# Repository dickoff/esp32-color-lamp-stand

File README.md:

# Color Lamp Stand — User Guide

This illuminated stand connects to Wi-Fi and uses its 32 LEDs to show whether
a stock selected in the firmware is up or down: green for up, red for down, and
white when no current value is available. The stock cannot currently be changed
through the Wi-Fi setup page.

This is the default behavior, but you could modify the software to do something
completely different or custom with the LEDs and the Internet connection.

## Hardware

You need:

- A USB-C wall charger and a USB-C-to-USB-C cable. For full brightness, use a
  charger that provides **5 V at 3 A**.

Good options are:

- This [Anker 20 W USB-C charger kit](https://www.amazon.com/dp/B0CP7NWH6L),
  which includes two compact chargers and two cables. Each charger provides
  5 V at 3 A.
- The inexpensive [IKEA SJÖSS 20 W USB-C charger](https://www.ikea.com/us/en/p/sjoess-20w-1-port-usb-charger-10618445/),
  which also provides 5 V at 3 A. Its USB-C cable is sold separately.

Either option provides enough power for the stand's highest brightness setting.
A computer USB-C port also works, but the stand may automatically use a lower
brightness if the port advertises less available current.

Feed the cable through the base and tie a loose knot inside for strain relief,
as shown below. Do not pull the knot tight enough to damage the cable.

Connect the USB-C plug to the socket on the circuit board.

Fit the translucent cover, then place the object you want to illuminate on top.

## Wi-Fi configuration

On first use, an amber wave travels around the stand and it creates a temporary
Wi-Fi network named
`ColorLamp-Setup-XXXX`, where the last four characters are unique to your stand.

1. On a phone, tablet, or computer, open Wi-Fi settings and join that network.
   It intentionally has no password and may be described by your device as
   having no internet.
2. The setup page should open automatically. If it does not, open
   [http://192.168.4.1](http://192.168.4.1) in a web browser.
3. Select your home Wi-Fi network, enter its password, and choose **Connect**.
4. The stand pulses blue while it tests the connection. Green means setup
   succeeded and the stand will restart. Red means it could not connect; check
   the network and password, then try again.

Your Wi-Fi password is stored only on the stand.

### Changing the Wi-Fi network

With the stand fully started, hold the **BOOT** button on the circuit board for
five seconds. The LEDs turn red, the saved Wi-Fi details are erased, and the
stand restarts in setup mode.

Do not hold **BOOT** while plugging in power or pressing **RESET**. That button
also activates the ESP32's programming mode during startup.

## What the lights during startup mean

Every startup shows the power check, then the firmware version, then the Wi-Fi
status.

### Power check

Immediately after power-on, a short sweep reports how much current the connected
USB-C source advertises. The stand uses this information to limit LED brightness.
The sweep fills, pauses for about a second, and fades away.

- **8 amber LEDs — USB default:** The stand uses a conservative, low-brightness
  limit. For better illumination, try a USB-C charger rated for at least 1.5 A.
- **16 cyan LEDs — 1.5 A:** Normal operation with good available brightness.
- **32 green LEDs — 3 A:** The source advertises the highest supported current.
- **Two red flashes, then 8 amber LEDs:** The stand could not read the source
  capability and safely selected the conservative limit.

This is the capability advertised by the power source, not a measurement of how
much current the stand is presently consuming.

### Firmware version

After the power check, three short displays show the firmware version in
**major.minor.patch** order. Count only the **bright white LEDs** in each display.
The rest of the ring glows dimly in a background color to identify the part:

- **Blue background:** Major version.
- **Purple background:** Minor version.
- **Amber background:** Patch version.

For example, version **2.2.0** shows two white LEDs on blue, two white LEDs on
purple, then an entirely dim amber ring. **No white LEDs means zero**—the colored
background still appears.

### Wi-Fi and setup

After the version display, the entire perimeter shows the Wi-Fi state.

- **Solid blue:** Connecting to the saved Wi-Fi network.
- **Slow amber wave (one lap every four seconds):** Waiting for you to join
  `ColorLamp-Setup-XXXX` and complete setup.
- **Pulsing blue:** Testing the Wi-Fi name and password you entered.
- **Solid green:** Connected successfully. After initial setup, the stand soon
  restarts automatically.
- **Solid red:** The attempted Wi-Fi connection failed.
- **Bright red after holding BOOT:** Saved Wi-Fi details are being erased.

## Troubleshooting

- **The setup page did not open:** Stay connected to `ColorLamp-Setup-XXXX` and
  open [http://192.168.4.1](http://192.168.4.1) manually. Temporarily disabling
  cellular data or a VPN can help if the phone leaves the setup network.
- **The stand keeps returning to amber setup mode:** Re-enter the Wi-Fi password
  and make sure the selected network is available where the stand will be used.
- **The light is unusually dim:** Check the power-on sweep. Eight amber LEDs mean
  the power source advertised only the default USB current; try another USB-C
  charger and cable.
- **You need to start over:** Let the stand finish booting, then hold **BOOT** for
  five seconds.

## Want to modify it?

The hardware and especially firmware are open for experimentation. See the
[modification guide](MODIFYING.md) for the source layout, fixed GPIO assignments,
KiCad design overview, and build workflow.

If you're working with an AI coding agent, point it at this repository and ask
it to read [MODIFYING.md](MODIFYING.md) before making changes.

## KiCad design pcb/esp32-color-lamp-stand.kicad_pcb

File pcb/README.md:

# PCB development

The KiCad project files and the project-local symbol library are the hardware
sources. Edit the schematic in KiCad, update the PCB with `F8`, and route or
refill zones in the PCB Editor.

KiCad 10 and Python 3 are required. On macOS the exporter finds KiCad in
`/Applications/KiCad`; elsewhere, put `kicad-cli` on `PATH` or set
`KICAD_CLI`.

From this directory:

```sh
make check
make manufacturing
```

`make check` runs schematic ERC and PCB DRC, including schematic/PCB parity.
Error-level violations block the command. The latest reports remain available
in `manufacturing/reports/`, including when a check fails. Review warnings in
KiCad before export.

`make manufacturing` performs the checks and writes these upload-ready files
to `manufacturing/jlcpcb/`:

- `esp32-color-lamp-stand-gerbers.zip`
- `jlcpcb_bom.csv`
- `jlcpcb_cpl.csv`
- top and bottom preview images

The exporter omits test points, requires an LCSC number for every assembled
part, and verifies that BOM and CPL designators match. Review the previews and
run JLCPCB's online DFM analysis before ordering.

Some JLCPCB/EasyEDA parts use placement origins or orientations that differ from
the corresponding KiCad footprints. Vendor-specific translation and rotation
corrections for those parts are documented in `jlcpcb-placement-offsets.toml`.
They change only the exported CPL; they do not move PCB footprints or alter the
Gerbers. The exporter looks up each correction by LCSC part number, verifies the
KiCad footprint named in the configuration, rotates local position offsets with
the component, and warns if the expected reference designators have changed.

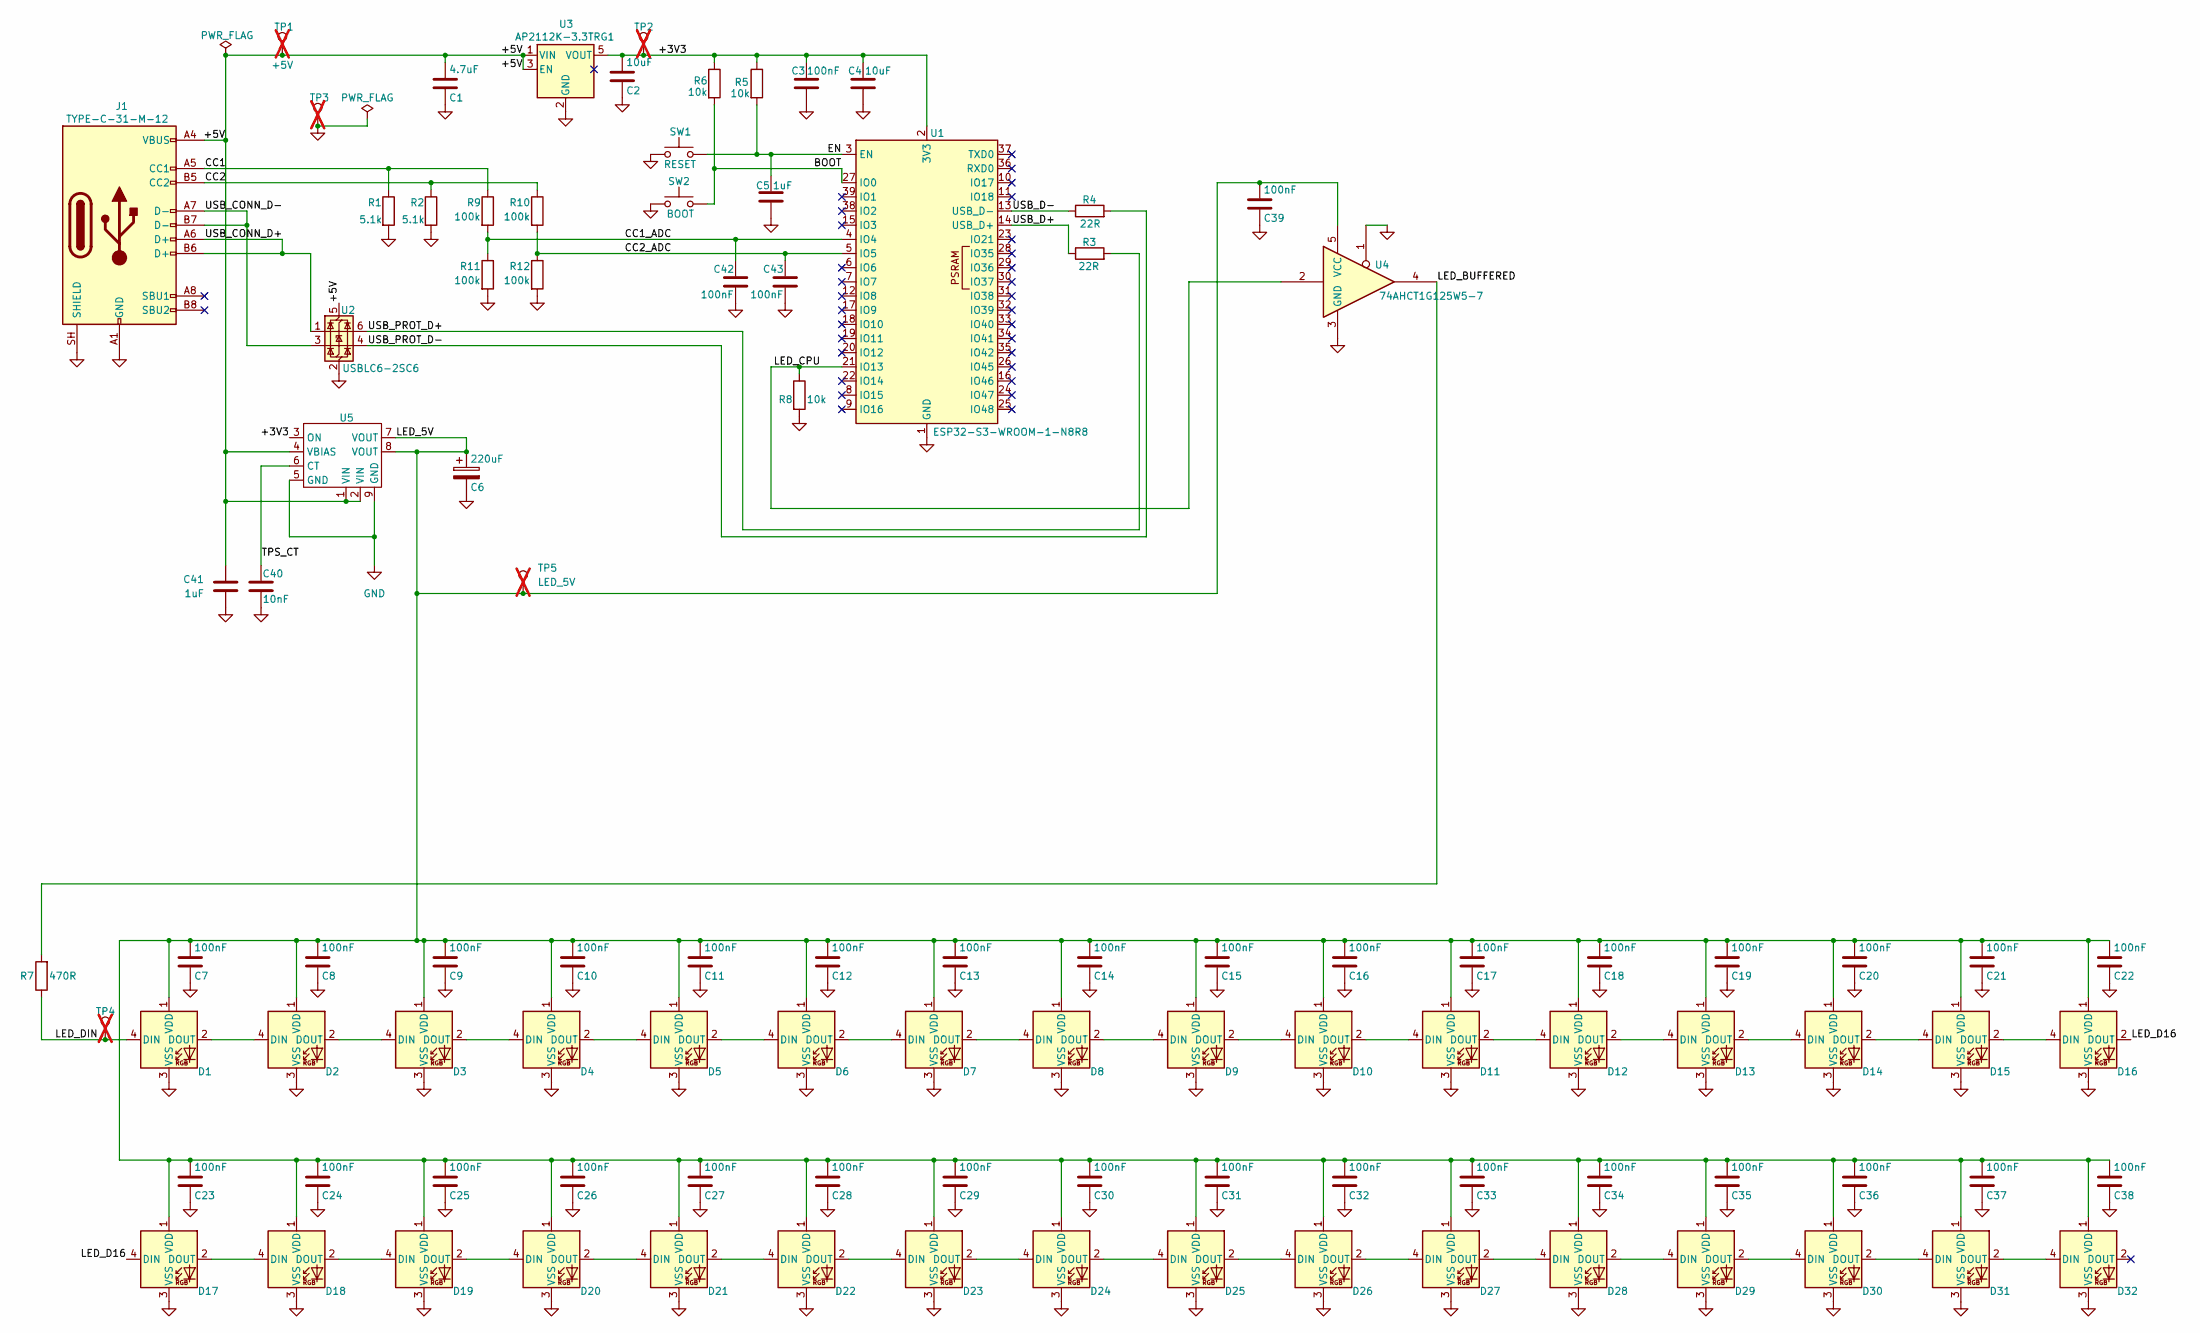
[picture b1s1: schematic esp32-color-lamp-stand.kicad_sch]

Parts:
C1: 4.7uF; C_0805_2012Metric; Manufacturer Part Number 4.7uF; LCSC C1779
C2, C4: 10uF; C_0805_2012Metric; Manufacturer Part Number 10uF; LCSC C15850
C3, C7, C8, C9, C10, C11, C12, C13, C14, C15, C16, C17, C18, C19, C20, C21, C22, C23, C24, C25, C26, C27, C28, C29, C30, C31, C32, C33, C34, C35, C36, C37, C38, C39: 100nF; C_0603_1608Metric; Manufacturer Part Number 100nF; LCSC C14663
C5: 1uF; C_0603_1608Metric; Manufacturer Part Number 1uF; LCSC C15849
C6: 220uF; C_Elec_6.3x5.8; Manufacturer Part Number RVT1A221M0605; LCSC C3345
C40: 10nF; C_0603_1608Metric; Manufacturer Part Number 10nF; LCSC C57112
C41: 1uF; C_0603_1608Metric; LCSC C15849
C42, C43: 100nF; C_0603_1608Metric; LCSC C14663
D1, D2, D3, D4, D5, D6, D7, D8, D9, D10, D11, D12, D13, D14, D15, D16, D17, D18, D19, D20, D21, D22, D23, D24, D25, D26, D27, D28, D29, D30, D31, D32: XL-5050RGBC-2812B-S; LED_WS2812B_PLCC4_5.0x5.0mm_P3.2mm; Manufacturer Part Number XL-5050RGBC-2812B-S; LCSC C22461793
J1: TYPE-C-31-M-12; USB_C_Receptacle_HRO_TYPE-C-31-M-12; Manufacturer Part Number TYPE-C-31-M-12; LCSC C165948
R1, R2: 5.1k; R_0603_1608Metric; Manufacturer Part Number 5.1k; LCSC C23186
R3, R4: 22R; R_0603_1608Metric; Manufacturer Part Number 22R; LCSC C23345
R5, R6, R8: 10k; R_0603_1608Metric; Manufacturer Part Number 10k; LCSC C25804
R7: 470R; R_0603_1608Metric; Manufacturer Part Number 470R; LCSC C23179
R9, R10, R11, R12: 100k; R_0603_1608Metric; Manufacturer Part Number 100k; LCSC C25803
SW1: RESET; SW_Push_1P1T_XKB_TS-1187A; Manufacturer Part Number TS-1187A-B-A-B; LCSC C318884
SW2: BOOT; SW_Push_1P1T_XKB_TS-1187A; Manufacturer Part Number TS-1187A-B-A-B; LCSC C318884
TP1: +5V; TestPoint_Pad_D1.0mm; not fitted
TP2: +3V3; TestPoint_Pad_D1.0mm; not fitted
TP3: GND; TestPoint_Pad_D1.0mm; not fitted
TP4: LED_DIN; TestPoint_Pad_D1.0mm; not fitted
TP5: LED_5V; TestPoint_Pad_D1.0mm; not fitted
U1: ESP32-S3-WROOM-1-N8R8; ESP32-S3-WROOM-1; Manufacturer Part Number ESP32-S3-WROOM-1-N8R8; LCSC C2913201
U2: USBLC6-2SC6; SOT-23-6; Manufacturer Part Number USBLC6-2SC6; LCSC C7519
U3: AP2112K-3.3TRG1; SOT-23-5; Manufacturer Part Number AP2112K-3.3TRG1; LCSC C23380830
U4: 74AHCT1G125W5-7; SOT-23-5; Manufacturer Part Number 74AHCT1G125W5-7; LCSC C842287
U5: TPS22975DSGR; Texas_DSG0008A_WSON-8-1EP_2x2mm_P0.5mm_EP0.9x1.6mm; Manufacturer Part Number TPS22975DSGR; LCSC C524777

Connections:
/+3V3: C2.1, C3.1, C4.1, R5.1, R6.1, TP2.1 (1_1), U1.2 (3V3), U3.5 (VOUT), U5.3 (ON)
/+5V: C1.1, C41.1, J1.A4 (VBUS), J1.A9 (VBUS), J1.B4 (VBUS), J1.B9 (VBUS), TP1.1 (1_1), U2.5 (VBUS), U3.1 (VIN), U3.3 (EN), U5.1 (VIN), U5.2 (VIN), U5.4 (VBIAS)
/BOOT: R6.2, SW2.2, U1.27 (IO0)
/CC1: J1.A5 (CC1), R1.1, R9.1
/CC1_ADC: C42.1, R9.2, R11.1, U1.4 (IO4)
/CC2: J1.B5 (CC2), R2.1, R10.1
/CC2_ADC: C43.1, R10.2, R12.1, U1.5 (IO5)
/EN: C5.1, R5.2, SW1.2, U1.3 (EN)
/LED_5V: C6.1, C7.1, C8.1, C9.1, C10.1, C11.1, C12.1, C13.1, C14.1, C15.1, C16.1, C17.1, C18.1, C19.1, C20.1, C21.1, C22.1, C23.1, C24.1, C25.1, C26.1, C27.1, C28.1, C29.1, C30.1, C31.1, C32.1, C33.1, C34.1, C35.1, C36.1, C37.1, C38.1, C39.1, D1.1 (VDD), D2.1 (VDD), D3.1 (VDD), D4.1 (VDD), D5.1 (VDD), D6.1 (VDD), D7.1 (VDD), D8.1 (VDD), D9.1 (VDD), D10.1 (VDD), D11.1 (VDD), D12.1 (VDD), D13.1 (VDD), D14.1 (VDD), D15.1 (VDD), D16.1 (VDD), D17.1 (VDD), D18.1 (VDD), D19.1 (VDD), D20.1 (VDD), D21.1 (VDD), D22.1 (VDD), D23.1 (VDD), D24.1 (VDD), D25.1 (VDD), D26.1 (VDD), D27.1 (VDD), D28.1 (VDD), D29.1 (VDD), D30.1 (VDD), D31.1 (VDD), D32.1 (VDD), TP5.1 (1_1), U4.5 (VCC), U5.7 (VOUT), U5.8 (VOUT)
/LED_BUFFERED: R7.2, U4.4
/LED_CPU: R8.1, U1.21 (IO13), U4.2
/LED_D16: D16.2 (DOUT), D17.4 (DIN)
/LED_DIN: D1.4 (DIN), R7.1, TP4.1 (1_1)
/TPS_CT: C40.1, U5.6 (CT)
/USB_CONN_D+: J1.A6 (D+), J1.B6 (D+), U2.1 (I/O1)
/USB_CONN_D-: J1.A7 (D-), J1.B7 (D-), U2.3 (I/O2)
/USB_D+: R3.1, U1.14 (USB_D+)
/USB_D-: R4.1, U1.13 (USB_D-)
/USB_PROT_D+: R3.2, U2.6 (I/O1)
/USB_PROT_D-: R4.2, U2.4 (I/O2)
GND: C1.2, C2.2, C3.2, C4.2, C5.2, C6.2, C7.2, C8.2, C9.2, C10.2, C11.2, C12.2, C13.2, C14.2, C15.2, C16.2, C17.2, C18.2, C19.2, C20.2, C21.2, C22.2, C23.2, C24.2, C25.2, C26.2, C27.2, C28.2, C29.2, C30.2, C31.2, C32.2, C33.2, C34.2, C35.2, C36.2, C37.2, C38.2, C39.2, C40.2, C41.2, C42.2, C43.2, D1.3 (VSS), D2.3 (VSS), D3.3 (VSS), D4.3 (VSS), D5.3 (VSS), D6.3 (VSS), D7.3 (VSS), D8.3 (VSS), D9.3 (VSS), D10.3 (VSS), D11.3 (VSS), D12.3 (VSS), D13.3 (VSS), D14.3 (VSS), D15.3 (VSS), D16.3 (VSS), D17.3 (VSS), D18.3 (VSS), D19.3 (VSS), D20.3 (VSS), D21.3 (VSS), D22.3 (VSS), D23.3 (VSS), D24.3 (VSS), D25.3 (VSS), D26.3 (VSS), D27.3 (VSS), D28.3 (VSS), D29.3 (VSS), D30.3 (VSS), D31.3 (VSS), D32.3 (VSS), J1.A1 (GND), J1.A12 (GND), J1.B1 (GND), J1.B12 (GND), J1.SH (SHIELD), R1.2, R2.2, R8.2, R11.2, R12.2, SW1.1, SW2.1, TP3.1 (1_1), U1.1 (GND), U1.40 (GND), U1.41 (GND), U2.2 (GND), U3.2 (GND), U4.1, U4.3 (GND), U5.5 (GND), U5.9 (GND)
unnamed: D1.2 (DOUT), D2.4 (DIN)
unnamed: D2.2 (DOUT), D3.4 (DIN)
unnamed: D3.2 (DOUT), D4.4 (DIN)
unnamed: D4.2 (DOUT), D5.4 (DIN)
unnamed: D5.2 (DOUT), D6.4 (DIN)
unnamed: D6.2 (DOUT), D7.4 (DIN)
unnamed: D7.2 (DOUT), D8.4 (DIN)
unnamed: D8.2 (DOUT), D9.4 (DIN)
unnamed: D9.2 (DOUT), D10.4 (DIN)
unnamed: D10.2 (DOUT), D11.4 (DIN)
unnamed: D11.2 (DOUT), D12.4 (DIN)
unnamed: D12.2 (DOUT), D13.4 (DIN)
unnamed: D13.2 (DOUT), D14.4 (DIN)
unnamed: D14.2 (DOUT), D15.4 (DIN)
unnamed: D15.2 (DOUT), D16.4 (DIN)
unnamed: D17.2 (DOUT), D18.4 (DIN)
unnamed: D18.2 (DOUT), D19.4 (DIN)
unnamed: D19.2 (DOUT), D20.4 (DIN)
unnamed: D20.2 (DOUT), D21.4 (DIN)
unnamed: D21.2 (DOUT), D22.4 (DIN)
unnamed: D22.2 (DOUT), D23.4 (DIN)
unnamed: D23.2 (DOUT), D24.4 (DIN)
unnamed: D24.2 (DOUT), D25.4 (DIN)
unnamed: D25.2 (DOUT), D26.4 (DIN)
unnamed: D26.2 (DOUT), D27.4 (DIN)
unnamed: D27.2 (DOUT), D28.4 (DIN)
unnamed: D28.2 (DOUT), D29.4 (DIN)
unnamed: D29.2 (DOUT), D30.4 (DIN)
unnamed: D30.2 (DOUT), D31.4 (DIN)
unnamed: D31.2 (DOUT), D32.4 (DIN)

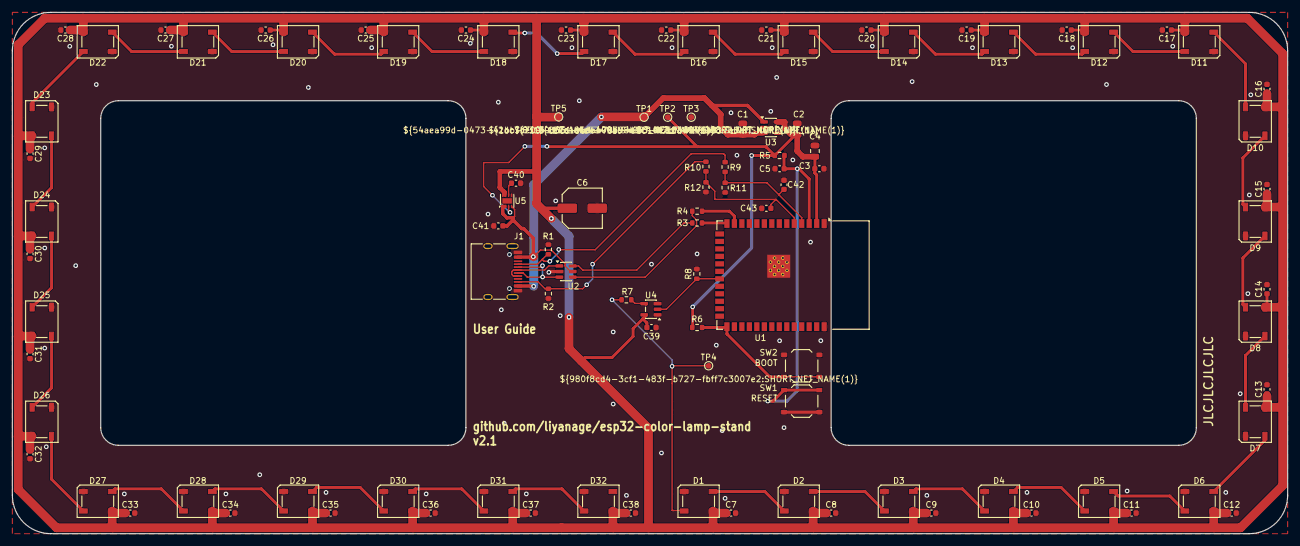
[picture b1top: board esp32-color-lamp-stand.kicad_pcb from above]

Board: 2 copper layers, 216.5 x 88.5 mm, 100 parts (0 on the bottom side), 51 nets.
